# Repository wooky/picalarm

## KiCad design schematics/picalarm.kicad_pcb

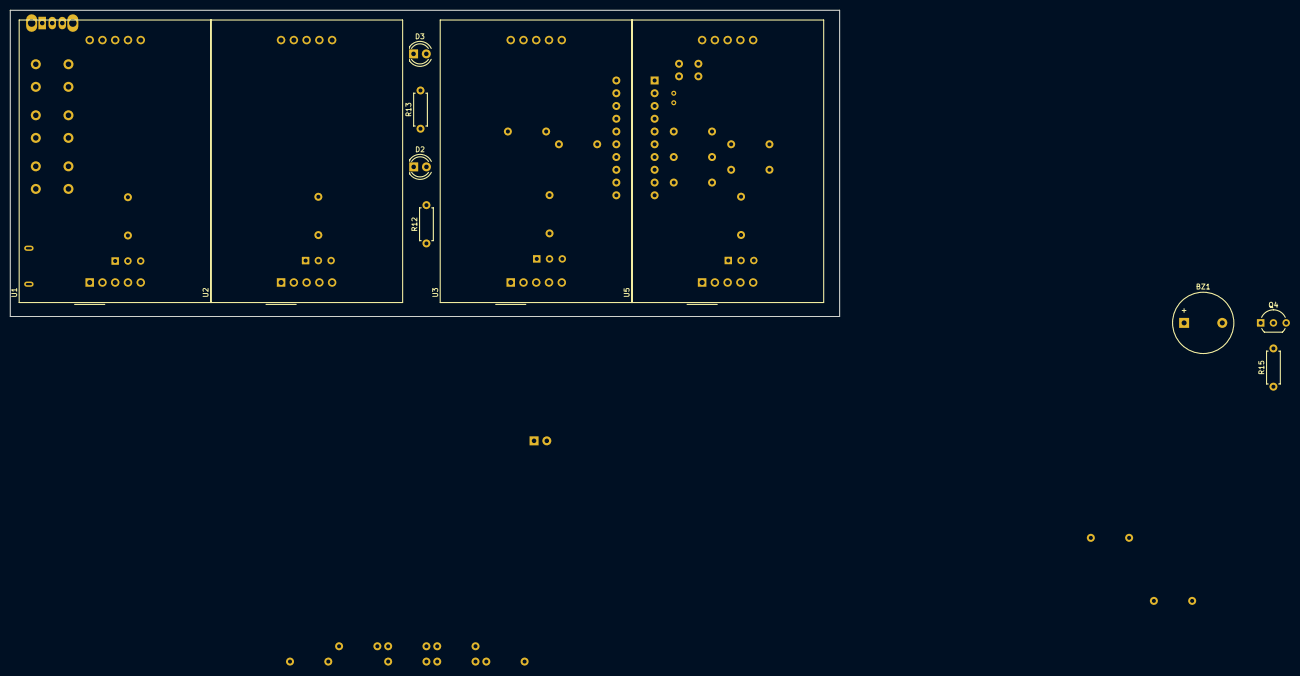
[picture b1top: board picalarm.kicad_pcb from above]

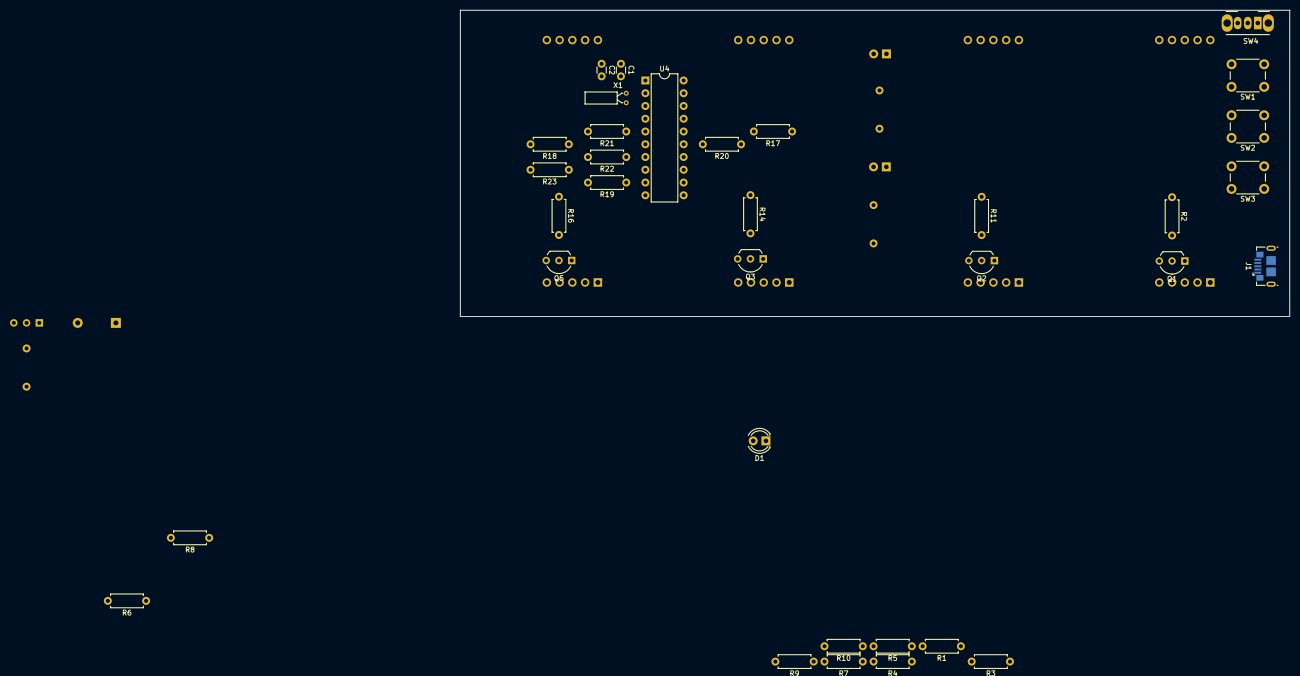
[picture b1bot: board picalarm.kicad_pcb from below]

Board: 2 copper layers, 165.1 x 61.0 mm, 45 parts (34 on the bottom side), 46 nets, no tracks yet.

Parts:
BZ1: Buzzer; Buzzer_12x9.5RM7.6
C1: 0.1µF; C_Disc_D3.0mm_W1.6mm_P2.50mm
C2: 0.01µF; C_Disc_D3.0mm_W1.6mm_P2.50mm
D1, D2, D3: Red LED; LED_D4.0mm
J1: USB_B_Mini; USB_Micro-B_GCT_USB3076-30-A
Q1, Q2, Q3, Q4, Q5: Q_NPN_BCE; TO-92_Inline_Wide
R1, R3, R4, R5, R7, R8, R9, R10: 10k; R_Axial_DIN0207_L6.3mm_D2.5mm_P7.62mm_Horizontal
R2, R11, R14, R16: 10K; R_Axial_DIN0207_L6.3mm_D2.5mm_P7.62mm_Horizontal
R6, R12, R13: 160R; R_Axial_DIN0207_L6.3mm_D2.5mm_P7.62mm_Horizontal
R15: 1K; R_Axial_DIN0207_L6.3mm_D2.5mm_P7.62mm_Horizontal
R17, R18, R19, R20, R21, R22, R23: 100R; R_Axial_DIN0207_L6.3mm_D2.5mm_P7.62mm_Horizontal
SW1: Hour; SW_PUSH_6mm
SW2: Minute; SW_PUSH_6mm
SW3: Alarm Set; SW_PUSH_6mm
SW4: Alarm On; SW_CuK_OS102011MA1QN1_SPDT_Angled
U1, U2, U3, U5: 7Segment; SBC18-11SURKCGKWA
U4: PIC16F15344; DIP-20_W7.62mm
X1: 32.768 KHz; Crystal_DS26_D2.0mm_L6.0mm_Horizontal

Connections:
BTN_ALARM_ADJUST: R9.2, U4.17
BTN_HOUR: R7.2, U4.19
BTN_MINUTE: R8.2, U4.18
CATH_HOURS_ONES: R11.1, U4.10
CATH_HOURS_TENS: R2.1, U4.11
CATH_MINUTES_ONES: R16.1, U4.13
CATH_MINUTES_TENS: R14.1, U4.12
GND: D1.1, D2.1, D3.1, J1.5, Q1.1, Q2.1, Q3.1, Q4.1, Q5.1, R1.2, R3.2, R4.2, R5.2, U1.8, U1.9, U2.8, U3.8, U4.20, U5.8
unnamed: BZ1.2, Q4.3
unnamed: C1.2, C2.2
unnamed: D1.2, R6.2
unnamed: D2.2, R12.2
unnamed: D3.2, R13.2
unnamed: Q1.2, R2.2
unnamed: Q1.3, U1.1, U1.5
unnamed: Q2.2, R11.2
unnamed: Q2.3, U2.1, U2.5
unnamed: Q3.2, R14.2
unnamed: Q3.3, U3.1, U3.5
unnamed: Q4.2, R15.2
unnamed: Q5.2, R16.2
unnamed: Q5.3, U5.1, U5.5
unnamed: R1.1, SW4.1
unnamed: R3.1, R7.1, SW1.2
unnamed: R4.1, R8.1, SW2.2
unnamed: R5.1, R9.1, SW3.2
unnamed: R6.1, R10.1, SW4.2
unnamed: R15.1, U4.14
unnamed: R17.1, U4.16
unnamed: R18.1, U4.6
unnamed: R19.1, U4.9
unnamed: R20.1, U4.15
unnamed: R21.1, U4.5
unnamed: R22.1, U4.7
unnamed: R23.1, U4.8
unnamed: U4.2, X1.1
unnamed: U4.3, X1.2
SEGMENT_A: R18.2, U1.7, U2.7, U3.7, U5.7
SEGMENT_B: R17.2, U1.6, U2.6, U3.6, U5.6
SEGMENT_C: R21.2, U1.4, U2.4, U3.4, U5.4
SEGMENT_D: R22.2, U1.3, U2.3, U3.3, U5.3
SEGMENT_E: R19.2, U1.2, U2.2, U3.2, U5.2
SEGMENT_F: R12.1, R13.1, R23.2, U2.9, U3.9, U5.9
SEGMENT_G: R20.2, U1.10, U2.10, U3.10, U5.10
SWT_ALARM: R10.2, U4.4
VDD: BZ1.1, C1.1, C2.1, J1.1, SW1.1, SW2.1, SW3.1, SW4.3, U4.1

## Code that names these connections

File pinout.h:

#ifndef PICALARM_PINOUT_H_
#define	PICALARM_PINOUT_H_

#include <xc.h>

//The segments of an LED are defined as such:
//
//  TOP
// T   T
// L   R
//  MID
// B   B
// L   R
//  BOT
#define	LED_SEG_LAT       PORTC
#define	LED_SEG_TOP       _PORTC_RC4_MASK
#define	LED_SEG_TOP_LEFT  _PORTC_RC6_MASK
#define	LED_SEG_TOP_RIGHT _PORTC_RC0_MASK
#define	LED_SEG_MID       _PORTC_RC1_MASK
#define	LED_SEG_BOT_LEFT  _PORTC_RC7_MASK
#define	LED_SEG_BOT_RIGHT _PORTC_RC5_MASK
#define	LED_SEG_BOT       _PORTC_RC3_MASK

#define	CATHODE_LAT          PORTB
#define	CATHODE_HOURS_TENS   _PORTB_RB6_MASK
#define	CATHODE_HOURS_ONES   _PORTB_RB7_MASK
#define	CATHODE_MINUTES_TENS _PORTB_RB5_MASK
#define	CATHODE_MINUTES_ONES _PORTB_RB4_MASK

#define BUTTON_PORT      PORTA
#define	BTN_HOUR         _PORTA_RA0_MASK
#define	BTN_MINUTE       _PORTA_RA1_MASK
#define	BTN_ALARM_ADJUST _PORTA_RA2_MASK
#define	SWT_ALARM        _PORTA_RA3_MASK

#define SECONDS_INDICATOR_PORT  PORTA
#define SECONDS_INDICATOR_MASK  _PORTA_RA4_MASK

#endif  //PICALARM_PINOUT_H_

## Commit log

2018-02-13 Initial C rewrite
2018-02-13 Re-add LICENSE file
2018-02-20 Got it to run
    Doesn't mean it's working properly
2018-02-21 It's working
    ...whenever it feels like working, that is
2018-02-22 More accurate clock with blinking second indicator
2018-02-23 Cleanup and ANSI styling
2018-02-23 Use TIMER1 instead of WDT
    Although the WDT can be used as a (rather inaccurate) timer, it gets reset when entering sleep. Thus, the only thing it guaranteed was that sleeping took exactly as long as needed, while disregarding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
2018-02-23 Move source files, remove autogenerated IDE files
2018-02-23 Forgot to delete a file
2018-02-24 Fixed project structure
2018-02-24 Re-enabled button ticking
2018-02-24 Remove clearly unused variables
    Saved 6 bytes of memory right there!
2018-02-24 A more accurate timer
    Using TIMER1 is quite horrendous because by the time you reset it, some cycles have already elapsed!
    I should next consider TIMER0, which has a way to compare the timer value with a predetermined value.
2018-02-25 Using TIMER0 now
    Although we can't really do multiples of 1,000,000 us with this timer, and as such the actual seconds are less than a second, that's fine because we know exactly how big a tick is, and we can account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
2018-02-25 <stdint.h> all the things
2018-02-25 Fixed timing I think?
2018-02-27 Add "correction second"
    Upon analysis, the clock is ahead by a minute every 9 hours. Put it another way, ahead by a second every 9 minutes. I could fix that by not being a cheap bastard and buy a crystal oscillator, or I co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
2018-02-27 Perhaps made the timing more correct
2018-02-28 Enough hacks, just tune the oscillator
2018-02-28 Better timing
2018-10-11 Started making a schematics file
2018-10-11 Eliminated tabs
2018-10-11 Use hours tens' top-left segment as the seconds indicator
    This frees up one pin which will be used for other functions
2018-10-11 More schematics
2018-10-11 Alarm time adjustment and rendering
2018-10-12 Buzzer stub
2018-10-16 Completed schematic
2018-10-18 Generated netlist and PCB stub
2018-10-21 Some rearranging of PCB components
2018-10-21 More rearranging of PCB components
2019-01-15 Updated MPLAB
2019-01-15 Fixed new blinking seconds indicator
2019-01-15 Moved seconds indicator to segments.c because it's not really configurable
2019-02-13 Move seconds indicator to its own output, use timer not WDT
2019-02-16 Fix display of alarm time
2019-02-16 Rename BUTTON_PORT to BUTTON_LAT for consistency
2019-02-16 Miserable stub at starting the buzzer PWM
2019-02-16 Use TIMER0 as the primary timer
    ...again. TIMER2 is the only timer that can be used for PWM.
    Plus, it turns out less code is needed for setting up and waking up with
    TIMER0 than with TIMER2.
2019-02-21 Update to XC8 v2.0, C99 compiler
2019-02-21 Attempt to set up PWM timing
2020-07-16 PIC16F73 port
2020-07-17 Use CCP for a more accurate timer
2020-07-20 Implement IDE simulation mode
2020-07-20 Centralize timing constants
2020-07-20 Memory "optimization"
    Saving a whopping 3 bytes
2020-07-20 Remove "ghost" LED segment
2020-07-20 Horrendous failure of a refactor
2020-07-20 Memory optimization
    8 bytes! That's over 4%!!!
2020-07-20 Some bug fixes which barely help
2020-07-20 Fix indescribably weird behavior
